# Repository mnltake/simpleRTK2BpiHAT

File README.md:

# simpleRTK2BpiHAT
simpleRTK2B（F9P）https://www.ardusimple.com/product/simplertk2b/

raspberryPi3A+ HAT

for gpsnavi https://github.com/mnltake/gpsnavi

-connect pi UART(GPIO14/15) to F9P UART1

-pull out I2C(GPIO2/3)

-pull out shutdownswitch (GPIO3/4/17)

-pull out keypad(GPIO9/11/5/6/13/19/26)

-pull out  led(GPIO21/20/16/12/7/8/25/27/22/24/23)

-pull out neopixel grove connector (GPIO18)

-pull out workswitch (GPIO10) and +12V relay 

Case 3Dprinter stl files

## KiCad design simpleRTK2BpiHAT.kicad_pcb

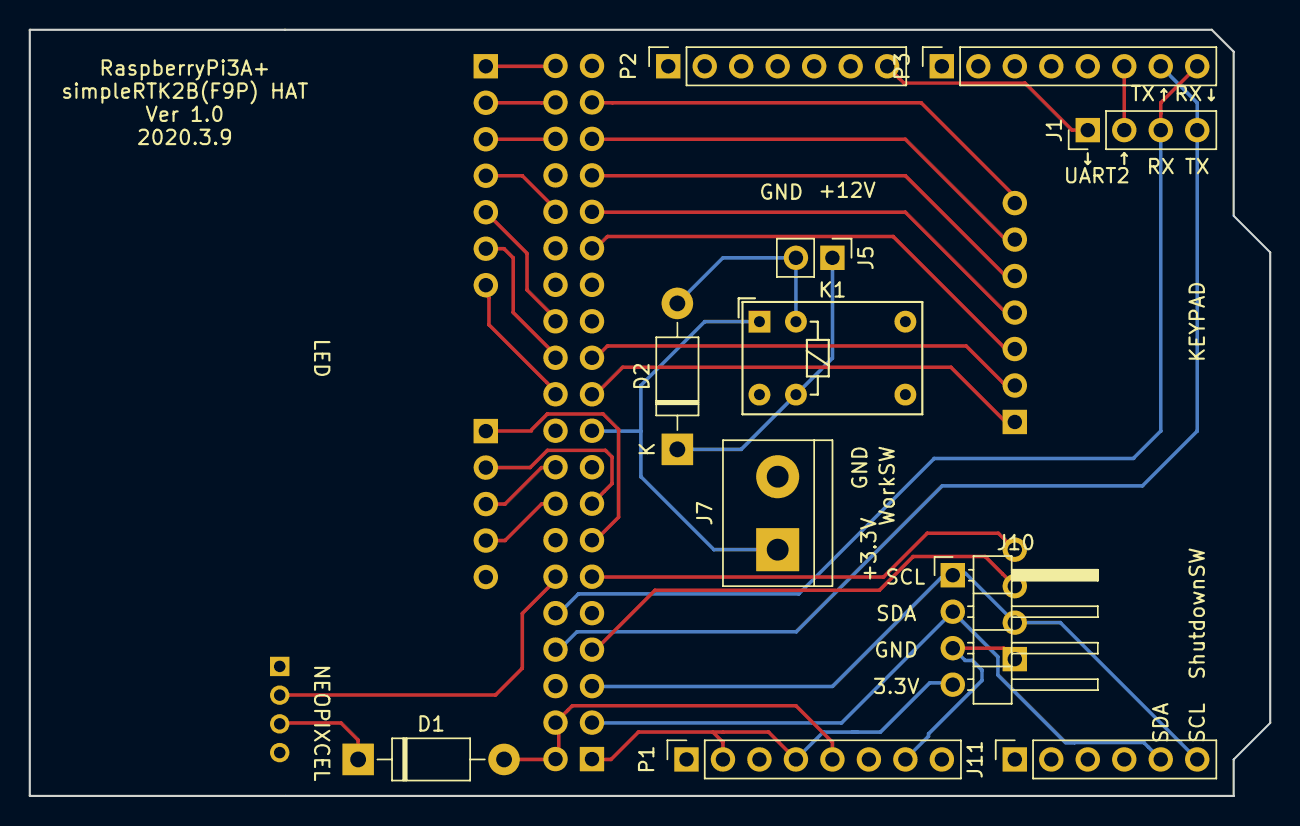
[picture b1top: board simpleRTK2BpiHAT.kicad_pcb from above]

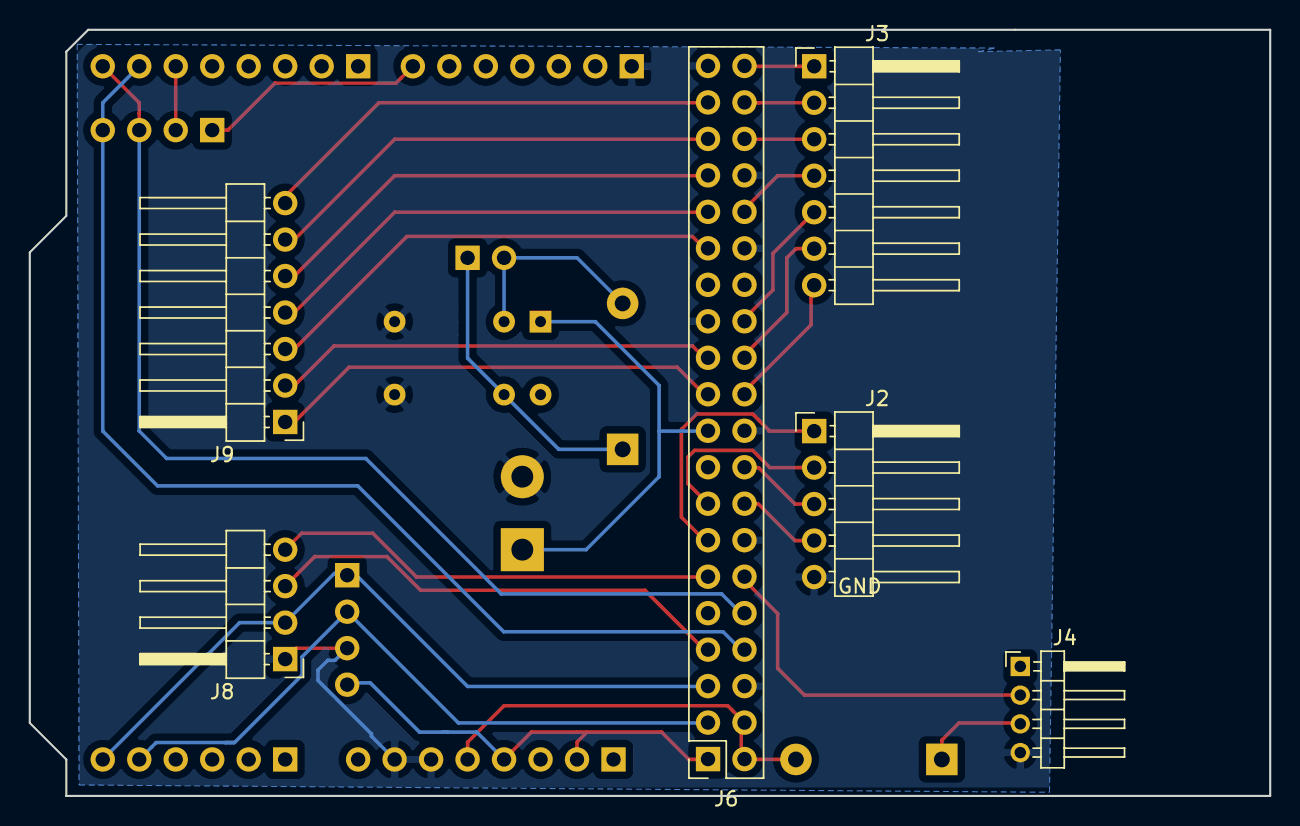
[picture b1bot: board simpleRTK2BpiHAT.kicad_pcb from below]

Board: 2 copper layers, 86.4 x 53.3 mm, 17 parts (6 on the bottom side), 34 nets.

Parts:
D1, D2: D; D_DO-41_SOD81_P10.16mm_Horizontal
J1: Conn_01x04; PinHeader_1x04_P2.54mm_Vertical
J2: Conn_01x05; PinHeader_1x05_P2.54mm_Horizontal
J3, J9: Conn_01x07; PinHeader_1x07_P2.54mm_Horizontal
J4: Conn_01x04; PinHeader_1x04_P2.00mm_Horizontal
J5: Screw_Terminal_01x02; PinHeader_1x02_P2.54mm_Vertical
J6: Raspberry_Pi_2_3; PinSocket_2x20_P2.54mm_Vertical
J7: Conn_01x02; TerminalBlock_bornier-2_P5.08mm
J8, J10: Conn_01x04; PinHeader_1x04_P2.54mm_Horizontal
J11: Conn_01x06; PinSocket_1x06_P2.54mm_Vertical
K1: Y14x-1C-xxDS; Relay_SPDT_HsinDa_Y14
P1: Power; PinSocket_1x08_P2.54mm_Vertical
P2: Digital; PinSocket_1x07_P2.54mm_Vertical
P3: Digital; PinSocket_1x08_P2.54mm_Vertical

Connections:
+3V3: J6.1, J10.4, P1.2, P1.4
+5V: D1.2, J6.2, J6.4, P1.5
GND: J2.5, J4.4, J6.6, J6.14, J6.20, J6.25, J6.30, J6.34, J6.39, J7.2, J8.1, J10.3, K1.5, K1.6, P1.6, P1.7, P2.1
GPIO2: J6.3, J10.2, J11.5
GPIO3: J6.5, J8.2, J10.1, J11.6
GPIO4: J6.7, J8.3
GPIO5: J6.29, J9.3
GPIO6: J6.31, J9.4
GPIO7: J3.5, J6.26
GPIO8: J3.6, J6.24
GPIO9: J6.21, J9.1
GPIO10: J6.19, J7.1, K1.1
GPIO11: J6.23, J9.2
GPIO12: J3.4, J6.32
GPIO13: J6.33, J9.5
GPIO14: J1.4, J6.8, P3.7
GPIO15: J1.3, J6.10, P3.8
GPIO16: J3.3, J6.36
GPIO17: J6.11, J8.4
GPIO18: J4.2, J6.12
GPIO19: J6.35, J9.6
GPIO20: J3.2, J6.38
GPIO21: J3.1, J6.40
GPIO22: J2.2, J6.15
GPIO23: J2.4, J6.16
GPIO24: J2.3, J6.18
GPIO25: J3.7, J6.22
GPIO26: J6.37, J9.7
GPIO27: J2.1, J6.13
unnamed: D1.1, J4.3
unnamed: D2.1, J5.1, K1.4
unnamed: D2.2, J5.2, K1.3
unnamed: J1.1, P2.7
unnamed: J1.2, P3.6

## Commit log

2020-03-09 create repository
2020-03-10 png update
2020-03-11 height +2mm
    高さ+2mm ドライバークリアランス
2020-03-20 shutdownSW GND
    shutdownSW のGNDがつながってなかった
